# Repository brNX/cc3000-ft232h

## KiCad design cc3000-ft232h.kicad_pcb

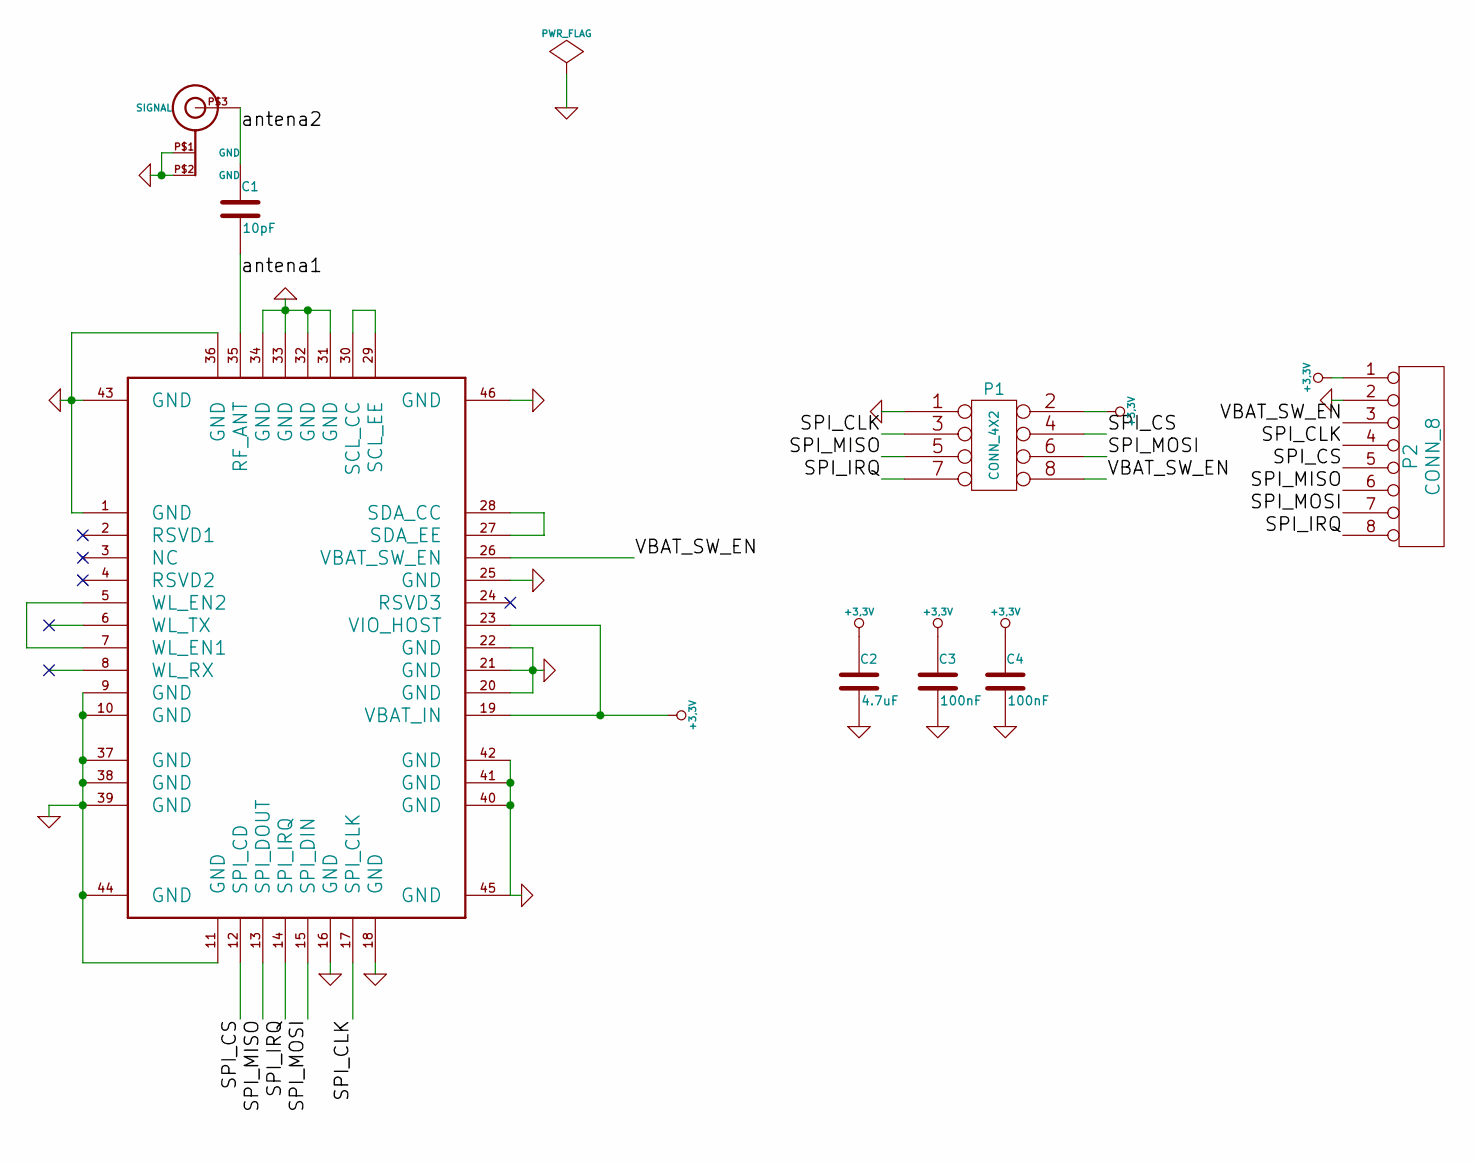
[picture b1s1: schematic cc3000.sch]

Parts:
C1: 10pF
C2: 4.7uF
C3, C4: 100nF
P1: CONN_4X2
P2: CONN_8
U1: U.FL_U.FL
U2: CC3000TEXAS_CC3000

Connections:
/cc3000/SPI_CLK: P1.3, P2.4, U2.17 (SPI_CLK)
/cc3000/SPI_CS: P1.4, P2.5, U2.12 (SPI_CD)
/cc3000/SPI_IRQ: P1.7, P2.8, U2.14 (SPI_IRQ)
/cc3000/SPI_MISO: P1.5, P2.6, U2.13 (SPI_DOUT)
/cc3000/SPI_MOSI: P1.6, P2.7, U2.15 (SPI_DIN)
/cc3000/VBAT_SW_EN: P1.8, P2.3, U2.26 (VBAT_SW_EN)
/cc3000/antena1: C1.2, U2.35 (RF_ANT)
/cc3000/antena2: C1.1, U1.P$3 (SIGNAL)
GND: C2.2, C3.2, C4.2, P1.1, P2.2, U1.P$1 (GND), U1.P$2 (GND), U2.1 (GND), U2.9 (GND), U2.10 (GND), U2.11 (GND), U2.16 (GND), U2.18 (GND), U2.20 (GND), U2.21 (GND), U2.22 (GND), U2.25 (GND), U2.31 (GND), U2.32 (GND), U2.33 (GND), U2.34 (GND), U2.36 (GND), U2.37 (GND), U2.38 (GND), U2.39 (GND), U2.40 (GND), U2.41 (GND), U2.42 (GND), U2.43 (GND), U2.44 (GND), U2.45 (GND), U2.46 (GND); also elsewhere on the board
unnamed: U2.5 (WL_EN2), U2.7 (WL_EN1)
unnamed: U2.27 (SDA_EE), U2.28 (SDA_CC)
unnamed: U2.29 (SCL_EE), U2.30 (SCL_CC)

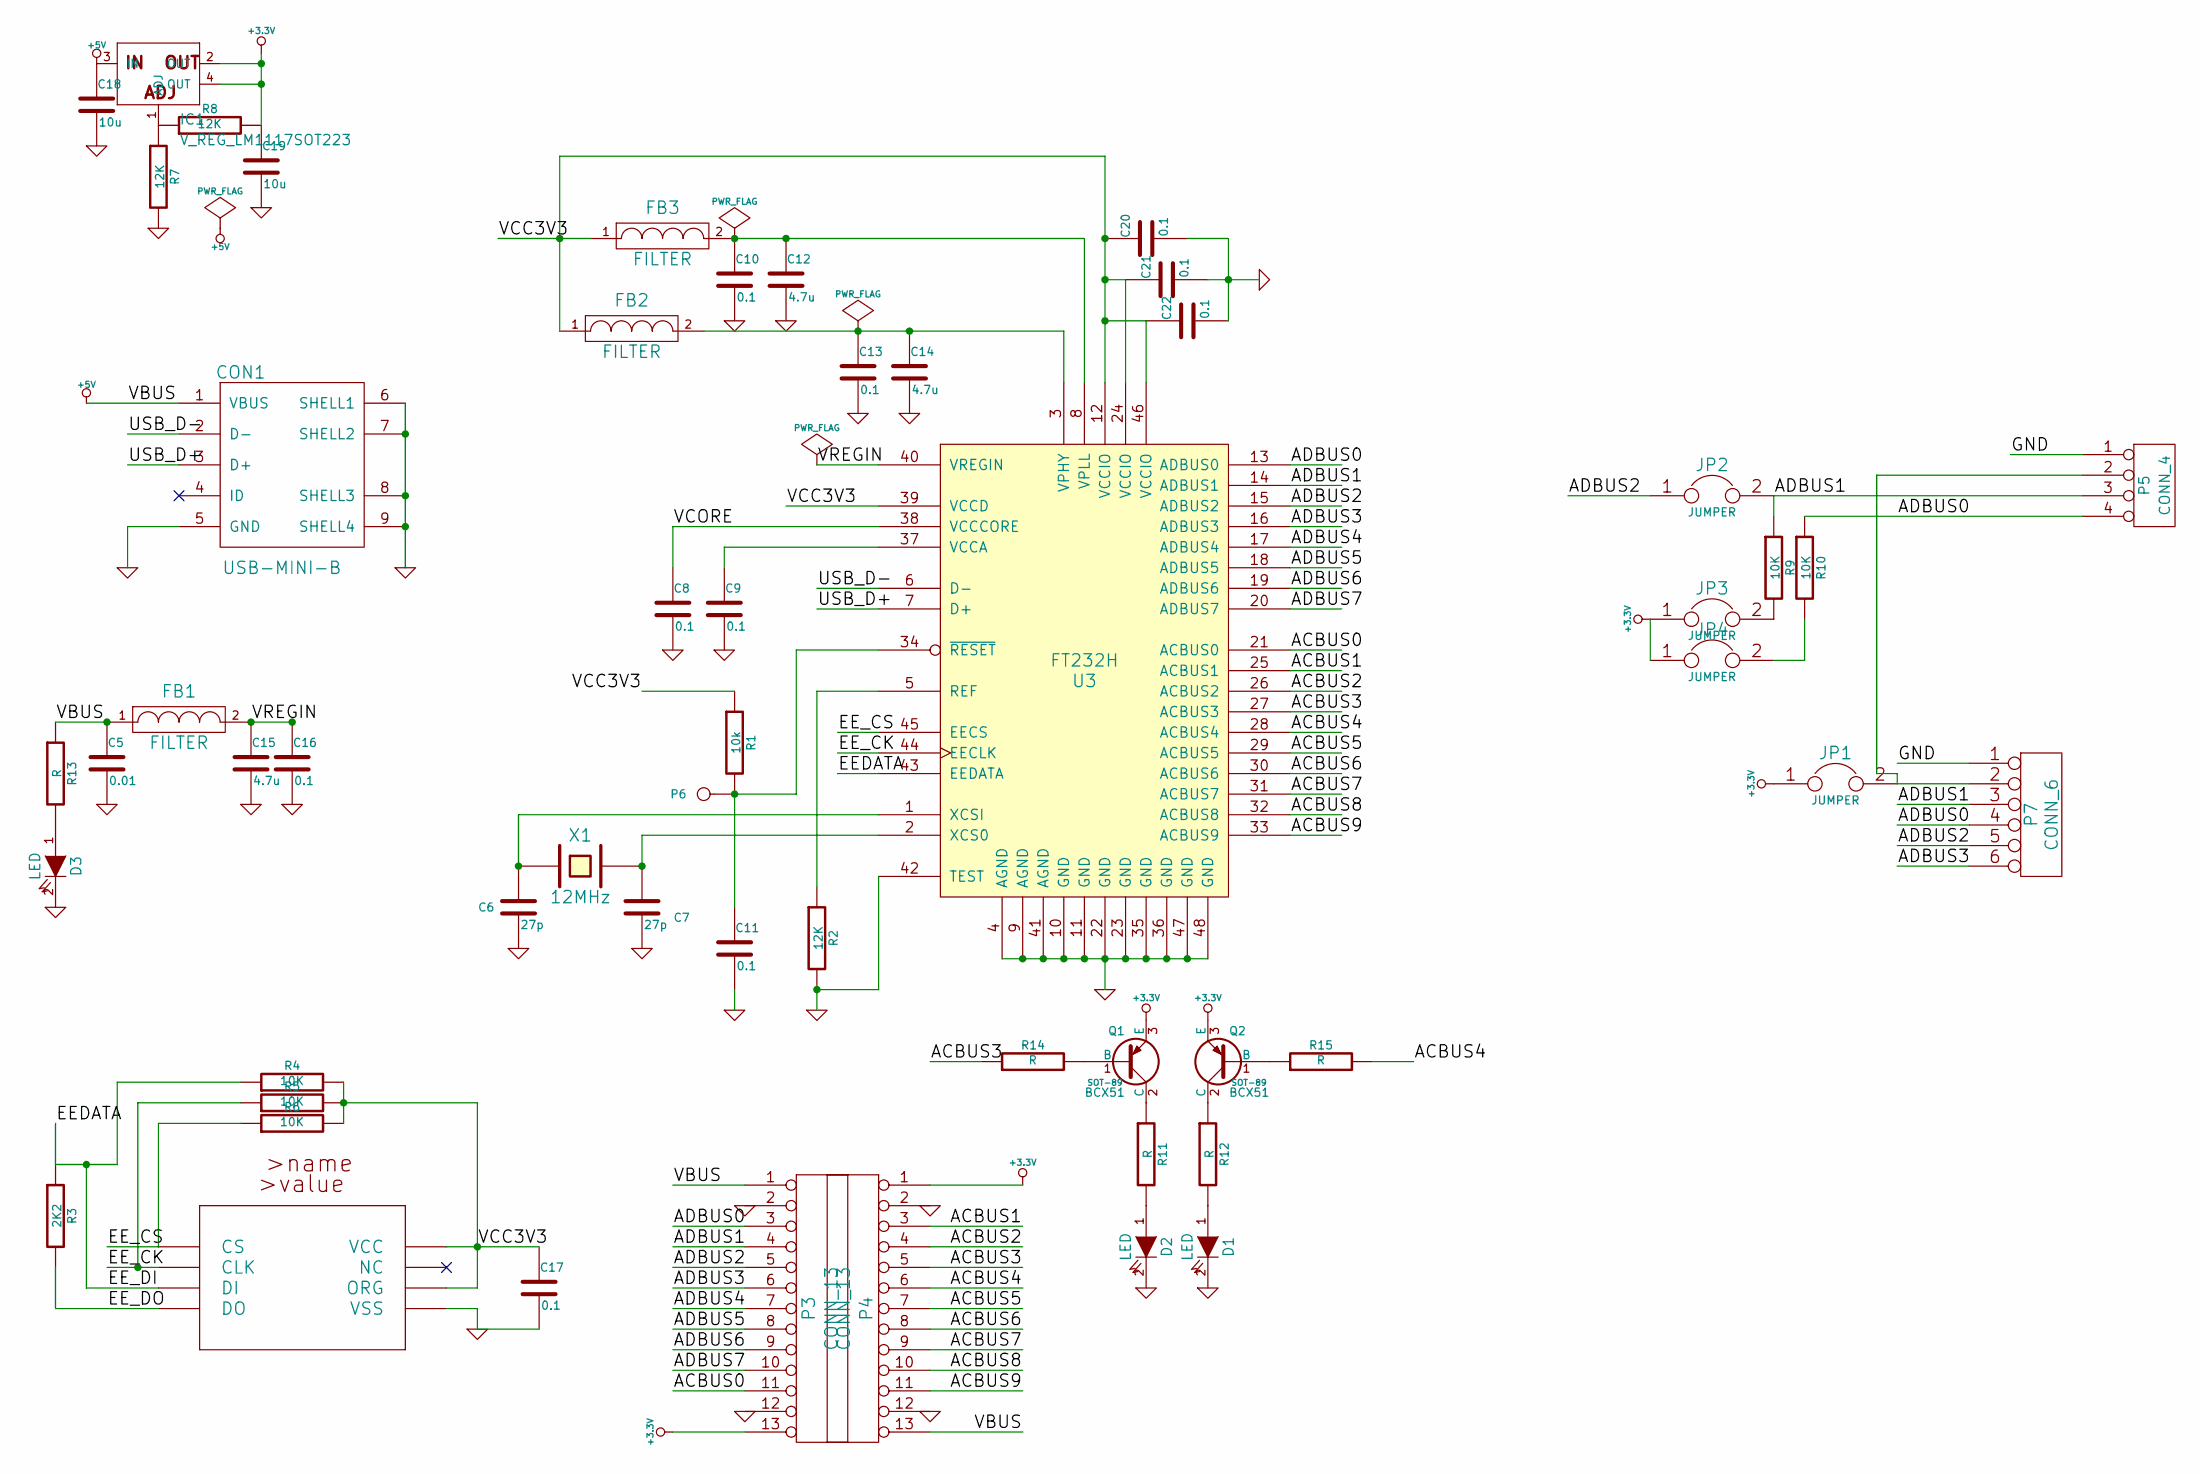
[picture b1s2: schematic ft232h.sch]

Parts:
C5: 0.01
C6, C7: 27p
C8, C9, C10, C11, C13, C16, C17, C20, C21, C22: 0.1
C12, C14, C15: 4.7u
C18, C19: 10u
CON1: USB-MINI-B
D1, D2, D3: LED
FB1, FB2, FB3: FILTER
IC1: V_REG_LM1117SOT223; SparkFun-SOT223
JP1, JP2, JP3, JP4: JUMPER
P3, P4: CONN_13
P5: CONN_4
P6: CONN_1
P7: CONN_6
Q1, Q2: BCX51; SOT-89
R1: 10k
R2, R7, R8: 12K
R3: 2K2
R4, R5, R6, R9, R10: 10K
R11, R12, R13, R14, R15: R
U3: FT232H
U5: 93LC56CX-X/SN_SOIC8-N_MC
X1: 12MHz

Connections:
+5V: C5.1, C18.1, CON1.1 (VBUS), FB1.1, IC1.3 (IN), P3.1, P4.13, R13.1
/ft232h/ACBUS0: P3.11, U3.21 (ACBUS0)
/ft232h/ACBUS1: P4.3, U3.25 (ACBUS1)
/ft232h/ACBUS2: P4.4, U3.26 (ACBUS2)
/ft232h/ACBUS3: P4.5, R14.1, U3.27 (ACBUS3)
/ft232h/ACBUS4: P4.6, R15.2, U3.28 (ACBUS4)
/ft232h/ACBUS5: P4.7, U3.29 (ACBUS5)
/ft232h/ACBUS6: P4.8, U3.30 (ACBUS6)
/ft232h/ACBUS7: P4.9, U3.31 (ACBUS7)
/ft232h/ACBUS8: P4.10, U3.32 (ACBUS8)
/ft232h/ACBUS9: P4.11, U3.33 (ACBUS9)
/ft232h/ADBUS0: P3.3, P5.4, P7.4, R10.1, U3.13 (ADBUS0)
/ft232h/ADBUS1: JP2.2, P3.4, P5.3, P7.3, R9.1, U3.14 (ADBUS1)
/ft232h/ADBUS2: JP2.1, P3.5, P7.5, U3.15 (ADBUS2)
/ft232h/ADBUS3: P3.6, P7.6, U3.16 (ADBUS3)
/ft232h/ADBUS4: P3.7, U3.17 (ADBUS4)
/ft232h/ADBUS5: P3.8, U3.18 (ADBUS5)
/ft232h/ADBUS6: P3.9, U3.19 (ADBUS6)
/ft232h/ADBUS7: P3.10, U3.20 (ADBUS7)
/ft232h/EEDATA: R3.1, R4.1, U3.43 (EEDATA), U5.3 (DI)
/ft232h/EE_CK: R5.1, U3.44 (EECLK), U5.2 (CLK)
/ft232h/EE_CS: R6.1, U3.45 (EECS), U5.1 (CS)
/ft232h/EE_DO: R3.2, U5.4 (DO)
/ft232h/USB_D+: CON1.3 (D+), U3.7 (D+)
/ft232h/USB_D-: CON1.2 (D-), U3.6 (D-)
/ft232h/VCC3V3: C17.1, C20.1, C21.1, C22.1, FB2.1, FB3.1, R1.1, R4.2, R5.2, R6.2, U3.12 (VCCIO), U3.24 (VCCIO), U3.39 (VCCD), U3.46 (VCCIO), U5.6 (ORG), U5.8 (VCC)
/ft232h/VCORE: C8.1, U3.38 (VCCCORE)
/ft232h/VREGIN: C15.1, C16.1, FB1.2, U3.40 (VREGIN)
GND: C5.2, C6.2, C7.2, C8.2, C9.2, C10.2, C11.2, C12.2, C13.2, C14.2, C15.2, C16.2, C17.2, C18.2, C19.2, C20.2, C21.2, C22.2, CON1.5 (GND), CON1.6 (SHELL1), CON1.7 (SHELL2), CON1.8 (SHELL3), CON1.9 (SHELL4), D1.2 (K), D2.2 (K), D3.2 (K), P3.2, P3.12, P4.2, P4.12, P5.1, P7.1, R2.2, R7.2, U3.4 (AGND), U3.9 (AGND), U3.10 (GND), U3.11 (GND), U3.22 (GND), U3.23 (GND), U3.35 (GND), U3.36 (GND), U3.41 (AGND), U3.42 (TEST), U3.47 (GND), U3.48 (GND), U5.5 (VSS); also elsewhere on the board
unnamed: Q1.2 (C), R11.1
unnamed: C11.1, P6.1, R1.2, U3.34 (~RESET)
unnamed: C7.1, U3.2 (XCS0), X1.2
unnamed: JP1.2, P5.2, P7.2
unnamed: C9.1, U3.37 (VCCA)
unnamed: R2.1, U3.5 (REF)
unnamed: D1.1 (A), R12.2
unnamed: D2.1 (A), R11.2
unnamed: Q2.2 (C), R12.1
unnamed: JP4.2, R10.2
unnamed: JP3.2, R9.2
unnamed: Q2.1 (B), R15.1
unnamed: Q1.1 (B), R14.2
unnamed: D3.1 (A), R13.2
unnamed: C6.1, U3.1 (XCSI), X1.1
unnamed: C13.1, C14.1, FB2.2, U3.3 (VPHY)
unnamed: C10.1, C12.1, FB3.2, U3.8 (VPLL)
unnamed: IC1.1 (ADJ), R7.1, R8.1

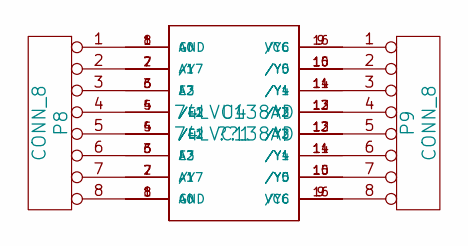
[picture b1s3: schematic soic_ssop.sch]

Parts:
??1: 74LVC138AD
P8, P9: CONN_8
U4: 74LVC138AD

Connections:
unnamed: ??1.15 (/Y0), P9.7, U4.10 (/Y5)
unnamed: ??1.16 (VCC), P9.8, U4.9 (/Y6)
unnamed: ??1.6 (E3), P8.3, U4.3 (A2)
unnamed: ??1.8 (GND), P8.1, U4.1 (A0)
unnamed: ??1.7 (/Y7), P8.2, U4.2 (A1)
unnamed: ??1.9 (/Y6), P9.1, U4.16 (VCC)
unnamed: ??1.14 (/Y1), P9.6, U4.11 (/Y4)
unnamed: ??1.13 (/Y2), P9.5, U4.12 (/Y3)
unnamed: ??1.12 (/Y3), P9.4, U4.13 (/Y2)
unnamed: ??1.11 (/Y4), P9.3, U4.14 (/Y1)
unnamed: ??1.10 (/Y5), P9.2, U4.15 (/Y0)
unnamed: ??1.5 (/E2), P8.4, U4.4 (/E1)
unnamed: ??1.4 (/E1), P8.5, U4.5 (/E2)
unnamed: ??1.3 (A2), P8.6, U4.6 (E3)
unnamed: ??1.2 (A1), P8.7, U4.7 (/Y7)
unnamed: ??1.1 (A0), P8.8, U4.8 (GND)

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
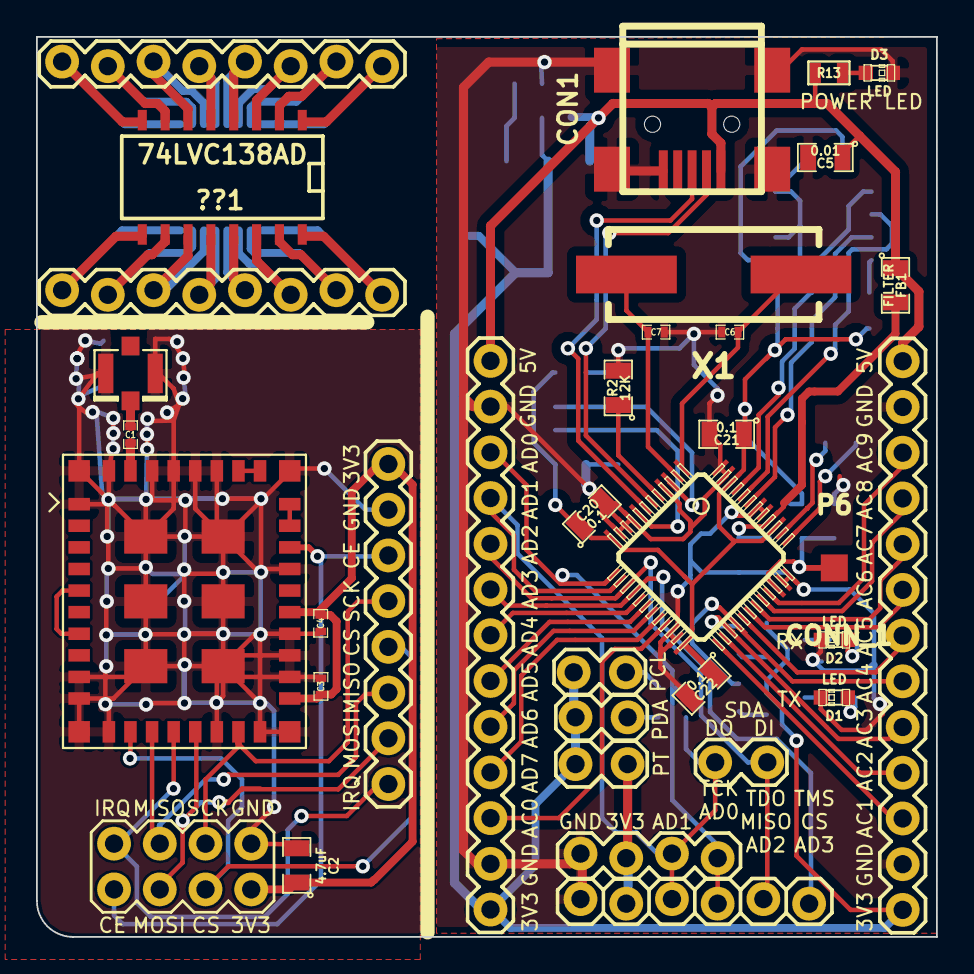
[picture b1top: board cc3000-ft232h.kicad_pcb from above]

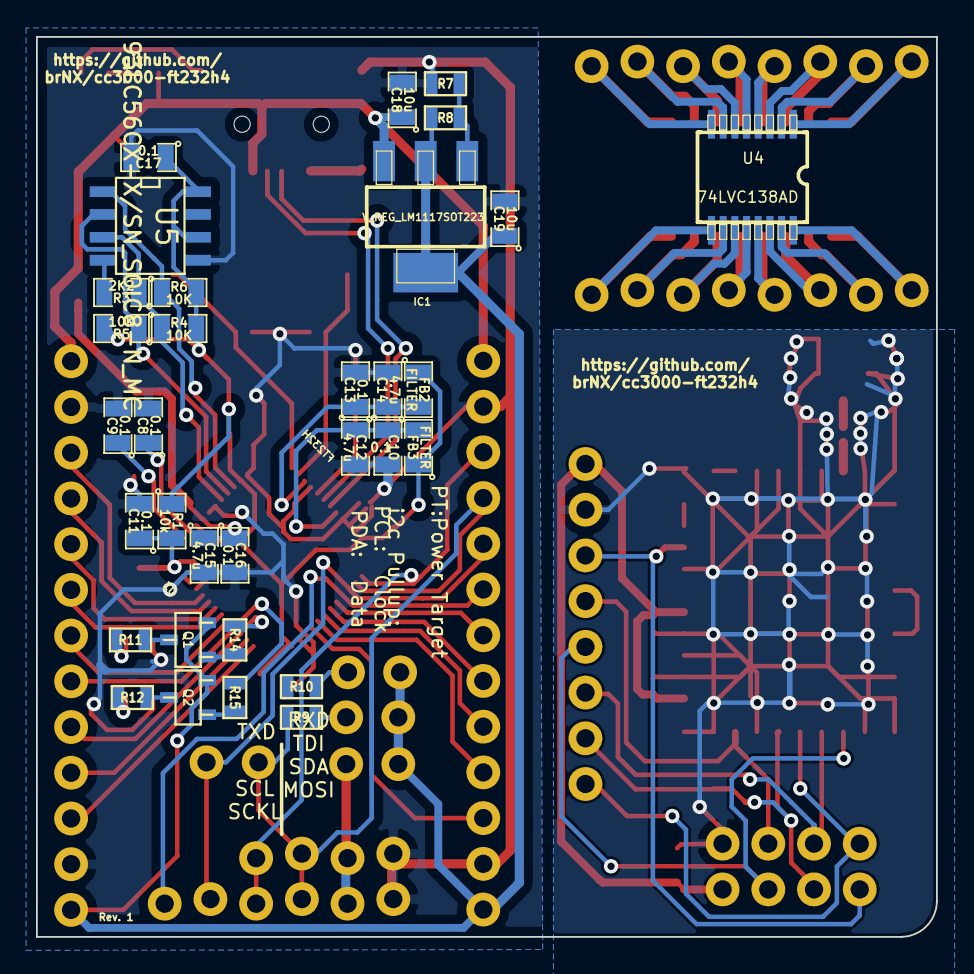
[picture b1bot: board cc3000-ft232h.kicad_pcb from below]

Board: 2 copper layers, 50.0 x 50.0 mm, 67 parts (32 on the bottom side), 75 nets.

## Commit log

2013-07-16 cc3000 breakout
2013-07-24 pinheader for breadboard
2013-07-31 added ft232h sheet
2013-08-01 files_added
2013-08-01 crystal lib added , fixed mini-usb
2013-08-02 headers
2013-08-02 faltam 20 ligaoes e caps mal
2013-08-03 ftdi pronto(versao beta) + breakout
2013-08-03 most erc errors fixed
2013-08-03 ftdi done + breakout done
2013-08-03 ftdi done + breakout done + silk done
2013-08-05 git link
2013-08-15 decoupling caps , silk screen modified
2013-08-15 via replaced
2013-08-22 gerber files
